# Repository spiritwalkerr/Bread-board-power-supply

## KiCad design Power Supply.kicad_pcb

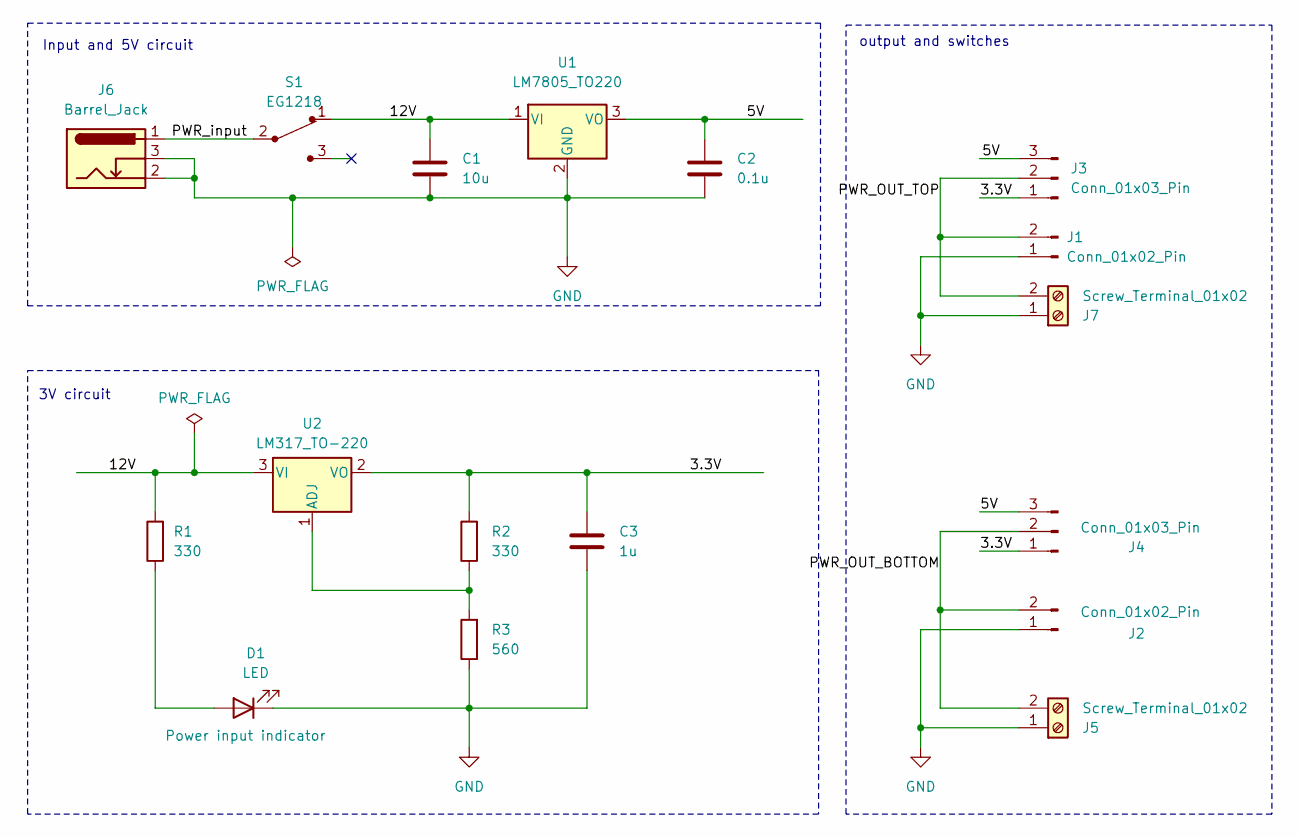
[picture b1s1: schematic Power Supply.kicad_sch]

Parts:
C1: 10u; C_Disc_D3.0mm_W1.6mm_P2.50mm
C2: 0.1u; C_Disc_D3.0mm_W1.6mm_P2.50mm
C3: 1u; C_Disc_D3.0mm_W1.6mm_P2.50mm
D1: LED; LED_D5.0mm_Clear
J1, J2: Conn_01x02_Pin; PinHeader_1x02_P2.54mm_Vertical
J3, J4: Conn_01x03_Pin; PinHeader_1x03_P2.54mm_Vertical
J5, J7: Screw_Terminal_01x02; TerminalBlock_bornier-2_P5.08mm
J6: Barrel_Jack; BarrelJack_Horizontal
R1, R2: 330; R_Axial_DIN0204_L3.6mm_D1.6mm_P7.62mm_Horizontal
R3: 560; R_Axial_DIN0204_L3.6mm_D1.6mm_P7.62mm_Horizontal
S1: EG1218; Switch_Slide_11.6x4mm_EG1218; MPN EG1218; Digi-Key_PN EG1903-ND
U1: LM7805_TO220; TO-220-3_Vertical
U2: LM317_TO-220; TO-220-3_Vertical

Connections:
/3.3V: C3.1, J3.1, J4.1, R2.2, U2.2 (VO)
/5V: C2.1, J3.3, J4.3, U1.3 (VO)
/12V: C1.1, R1.2, S1.1, U1.1 (VI), U2.3 (VI)
/PWR_OUT_BOTTOM: J2.2, J4.2, J5.2
/PWR_OUT_TOP: J1.2, J3.2, J7.2
/PWR_input: J6.1, S1.2
GND: C1.2, C2.2, C3.2, D1.1 (K), J1.1, J2.1, J5.1, J6.2, J6.3, J7.1, R3.1, U1.2 (GND)
unnamed: D1.2 (A), R1.1
unnamed: R2.1, R3.2, U2.1 (ADJ)

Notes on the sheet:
3V circuit
output and switches
Input and 5V circuit

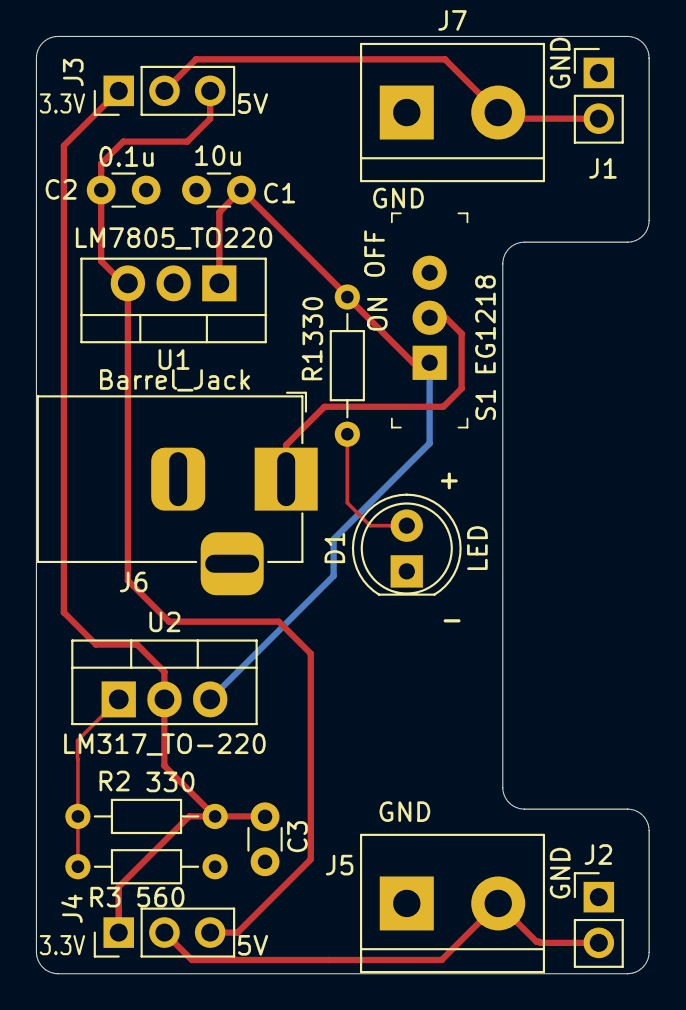
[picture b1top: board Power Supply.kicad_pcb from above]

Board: 2 copper layers, 34.0 x 52.1 mm, 17 parts (0 on the bottom side), 9 nets.

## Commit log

2025-02-27 just added a small text
2025-02-27 edited gitignore file
2025-02-27 added another text
2025-02-27 remove a text
2025-02-27 to test github
2025-02-27 moved text
